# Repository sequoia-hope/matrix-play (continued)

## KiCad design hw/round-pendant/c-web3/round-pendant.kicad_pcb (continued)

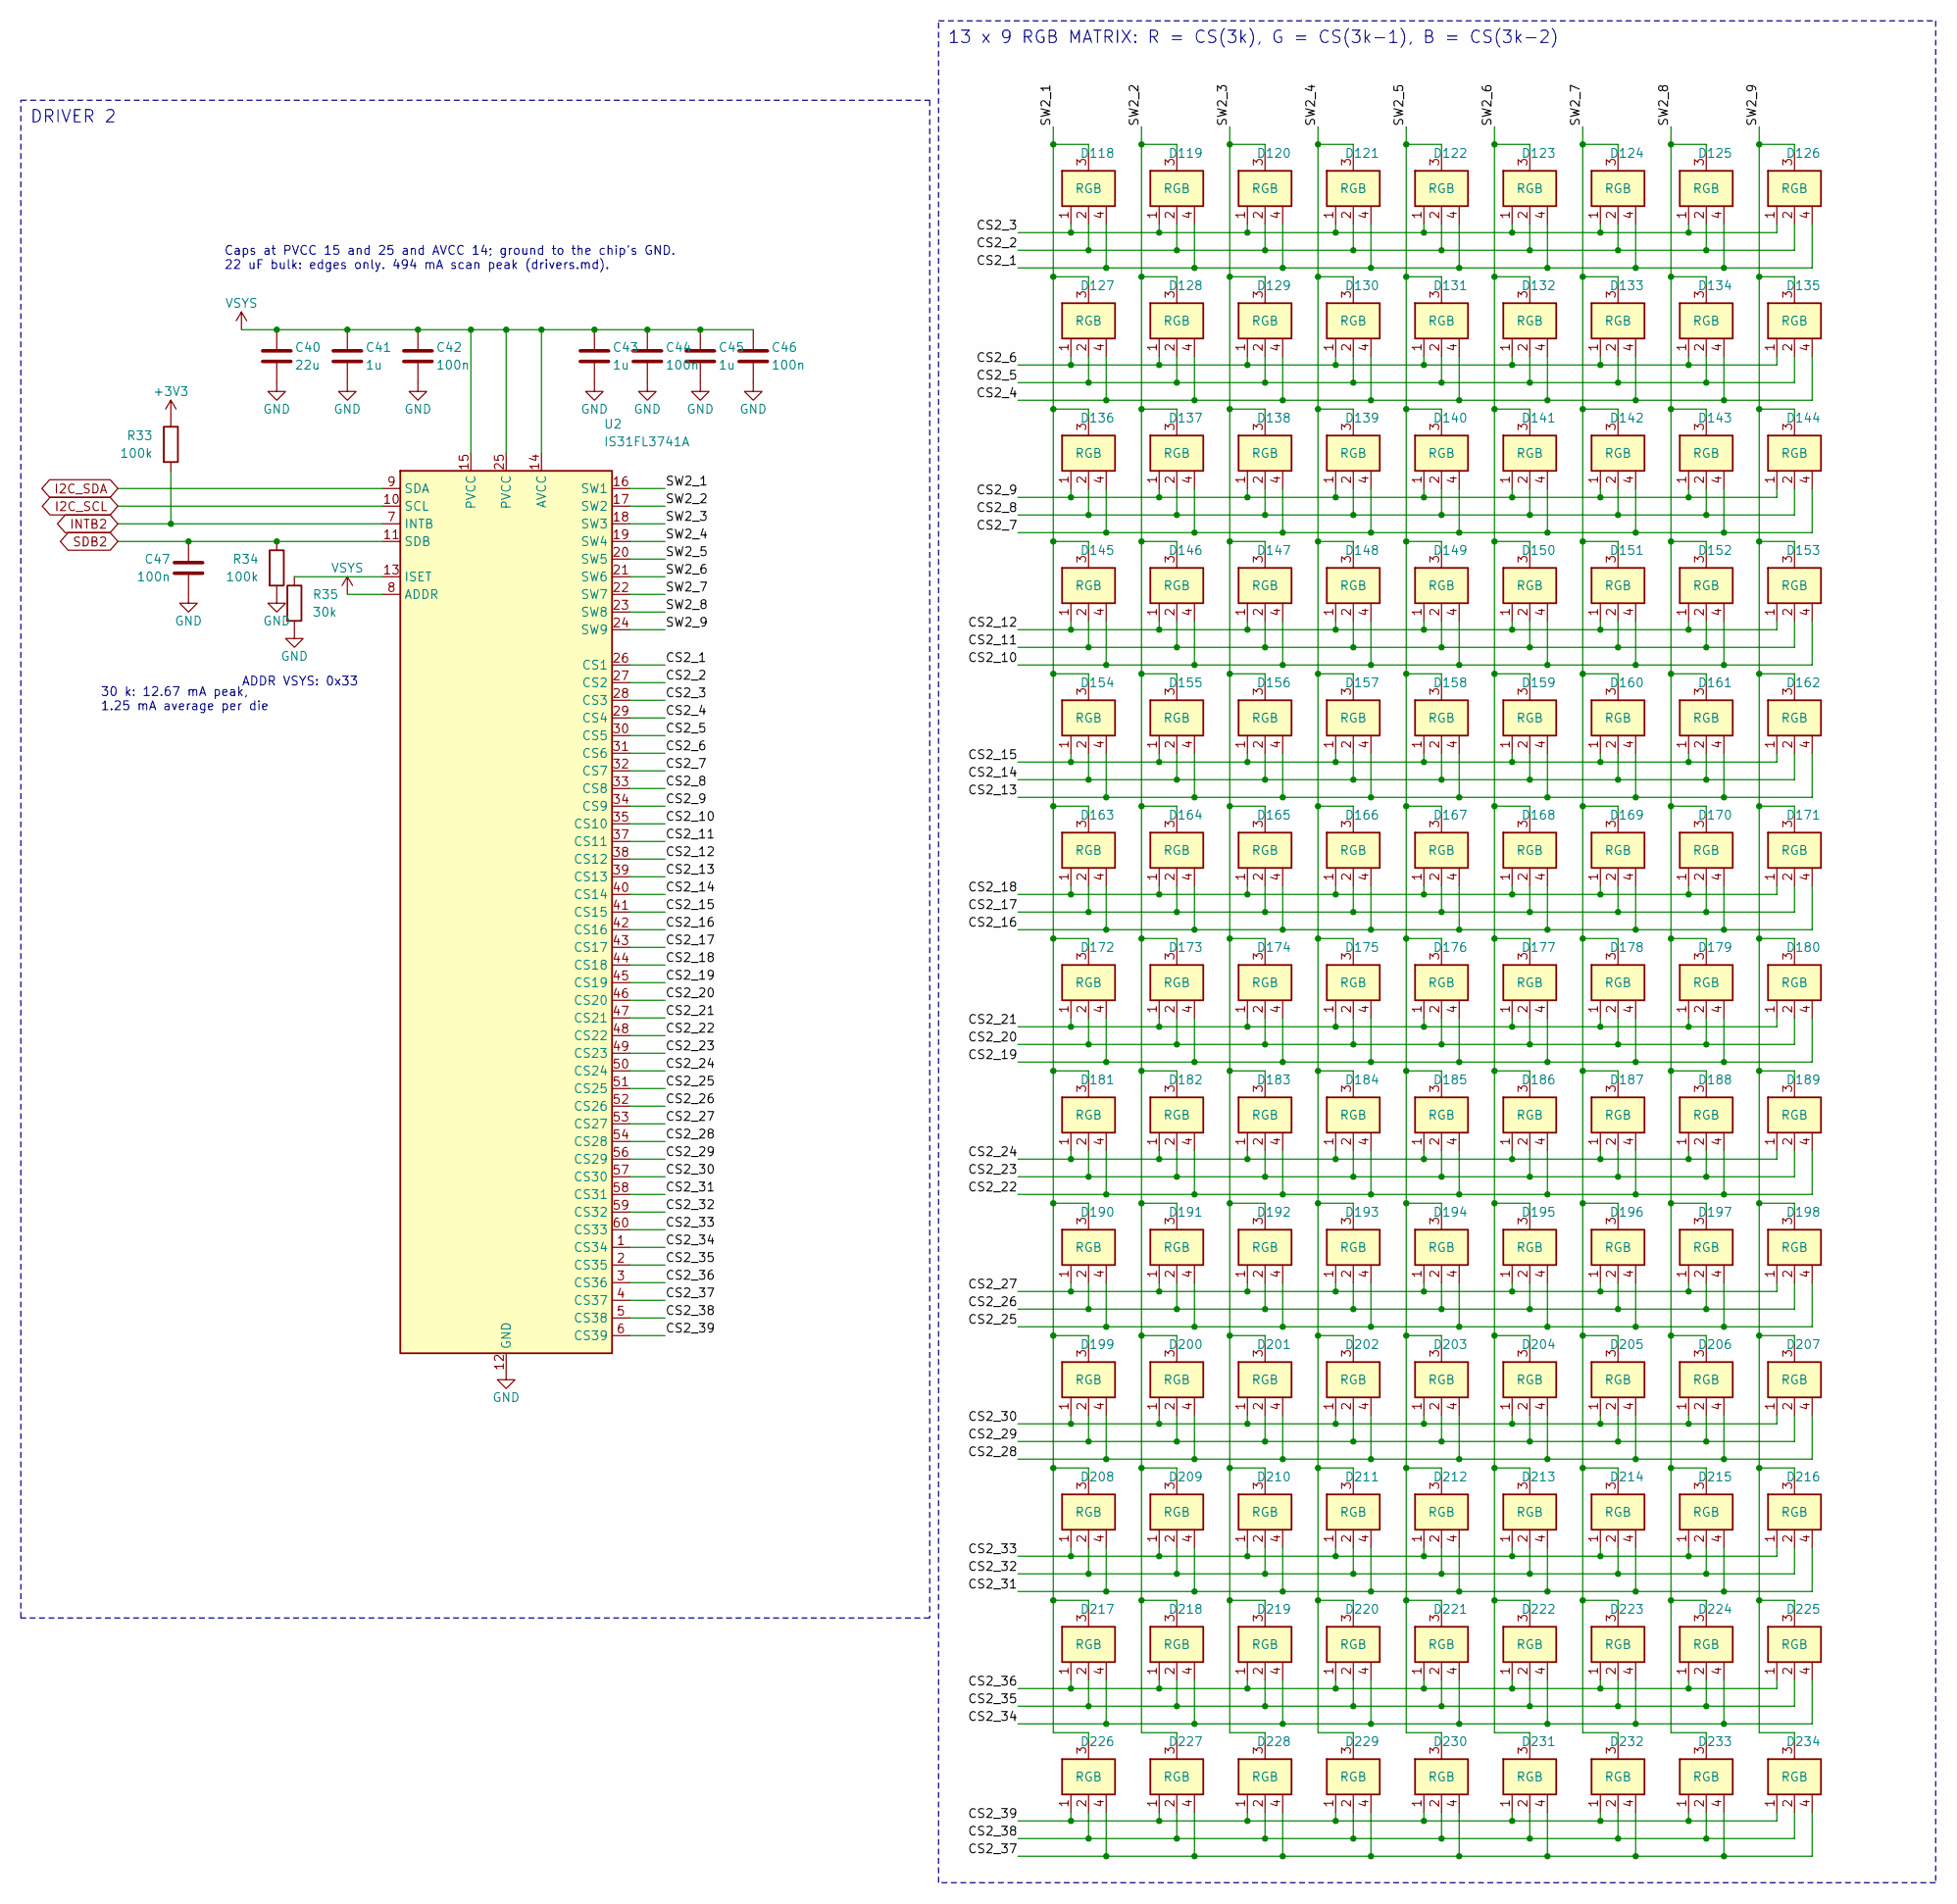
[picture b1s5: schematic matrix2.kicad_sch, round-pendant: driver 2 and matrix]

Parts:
C40: 22u; C_0603_1608Metric; MPN CL10A226MP8NUNE; LCSC C86295
C41, C43, C45: 1u; C_0402_1005Metric; MPN CL05A105KA5NQNC; LCSC C52923
C42, C44, C46, C47: 100n; C_0402_1005Metric; MPN CL05B104KO5NNNC; LCSC C1525
D118, D119, D120, D121, D122, D123, D124, D125, D126, D127, D128, D129, D130, D131, D132, D133, D134, D135, D136, D137, D138, D139, D140, D141, D142, D143, D144, D145, D146, D147, D148, D149, D150, D151, D152, D153, D154, D155, D156, D157, D158, D159, D160, D161, D162, D163, D164, D165, D166, D167, D168, D169, D170, D171, D172, D173, D174, D175, D176, D177, D178, D179, D180, D181, D182, D183, D184, D185, D186, D187, D188, D189, D190, D191, D192, D193, D194, D195, D196, D197, D198, D199, D200, D201, D202, D203, D204, D205, D206, D207, D208, D209, D210, D211, D212, D213, D214, D215, D216, D217, D218, D219, D220, D221, D222, D223, D224, D225, D226, D227, D228, D229, D230, D231, D232, D233, D234: RGB; LED_XL-1010RGB; MPN XL-1010RGB-YG; LCSC C965834
R33, R34: 100k; R_0402_1005Metric; MPN 0402WGF1003TCE; LCSC C25741
R35: 30k; R_0402_1005Metric; MPN 0402WGF3002TCE; LCSC C25776
U2: IS31FL3741A; QFN-60-1EP_7x7mm_P0.4mm_EP5.4x5.4mm; MPN IS31FL3741A-QFLS4-TR; LCSC C2940604

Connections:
+3V3: R33.1; also elsewhere on the board
/Driver 2 and matrix/CS2_1: D118.4 (B), D119.4 (B), D120.4 (B), D121.4 (B), D122.4 (B), D123.4 (B), D124.4 (B), D125.4 (B), D126.4 (B), U2.26 (CS1)
/Driver 2 and matrix/CS2_2: D118.2 (G), D119.2 (G), D120.2 (G), D121.2 (G), D122.2 (G), D123.2 (G), D124.2 (G), D125.2 (G), D126.2 (G), U2.27 (CS2)
/Driver 2 and matrix/CS2_3: D118.1 (R), D119.1 (R), D120.1 (R), D121.1 (R), D122.1 (R), D123.1 (R), D124.1 (R), D125.1 (R), D126.1 (R), U2.28 (CS3)
/Driver 2 and matrix/CS2_4: D127.4 (B), D128.4 (B), D129.4 (B), D130.4 (B), D131.4 (B), D132.4 (B), D133.4 (B), D134.4 (B), D135.4 (B), U2.29 (CS4)
/Driver 2 and matrix/CS2_5: D127.2 (G), D128.2 (G), D129.2 (G), D130.2 (G), D131.2 (G), D132.2 (G), D133.2 (G), D134.2 (G), D135.2 (G), U2.30 (CS5)
/Driver 2 and matrix/CS2_6: D127.1 (R), D128.1 (R), D129.1 (R), D130.1 (R), D131.1 (R), D132.1 (R), D133.1 (R), D134.1 (R), D135.1 (R), U2.31 (CS6)
/Driver 2 and matrix/CS2_7: D136.4 (B), D137.4 (B), D138.4 (B), D139.4 (B), D140.4 (B), D141.4 (B), D142.4 (B), D143.4 (B), D144.4 (B), U2.32 (CS7)
/Driver 2 and matrix/CS2_8: D136.2 (G), D137.2 (G), D138.2 (G), D139.2 (G), D140.2 (G), D141.2 (G), D142.2 (G), D143.2 (G), D144.2 (G), U2.33 (CS8)
/Driver 2 and matrix/CS2_9: D136.1 (R), D137.1 (R), D138.1 (R), D139.1 (R), D140.1 (R), D141.1 (R), D142.1 (R), D143.1 (R), D144.1 (R), U2.34 (CS9)
/Driver 2 and matrix/CS2_10: D145.4 (B), D146.4 (B), D147.4 (B), D148.4 (B), D149.4 (B), D150.4 (B), D151.4 (B), D152.4 (B), D153.4 (B), U2.35 (CS10)
/Driver 2 and matrix/CS2_11: D145.2 (G), D146.2 (G), D147.2 (G), D148.2 (G), D149.2 (G), D150.2 (G), D151.2 (G), D152.2 (G), D153.2 (G), U2.37 (CS11)
/Driver 2 and matrix/CS2_12: D145.1 (R), D146.1 (R), D147.1 (R), D148.1 (R), D149.1 (R), D150.1 (R), D151.1 (R), D152.1 (R), D153.1 (R), U2.38 (CS12)
/Driver 2 and matrix/CS2_13: D154.4 (B), D155.4 (B), D156.4 (B), D157.4 (B), D158.4 (B), D159.4 (B), D160.4 (B), D161.4 (B), D162.4 (B), U2.39 (CS13)
/Driver 2 and matrix/CS2_14: D154.2 (G), D155.2 (G), D156.2 (G), D157.2 (G), D158.2 (G), D159.2 (G), D160.2 (G), D161.2 (G), D162.2 (G), U2.40 (CS14)
/Driver 2 and matrix/CS2_15: D154.1 (R), D155.1 (R), D156.1 (R), D157.1 (R), D158.1 (R), D159.1 (R), D160.1 (R), D161.1 (R), D162.1 (R), U2.41 (CS15)
/Driver 2 and matrix/CS2_16: D163.4 (B), D164.4 (B), D165.4 (B), D166.4 (B), D167.4 (B), D168.4 (B), D169.4 (B), D170.4 (B), D171.4 (B), U2.42 (CS16)
/Driver 2 and matrix/CS2_17: D163.2 (G), D164.2 (G), D165.2 (G), D166.2 (G), D167.2 (G), D168.2 (G), D169.2 (G), D170.2 (G), D171.2 (G), U2.43 (CS17)
/Driver 2 and matrix/CS2_18: D163.1 (R), D164.1 (R), D165.1 (R), D166.1 (R), D167.1 (R), D168.1 (R), D169.1 (R), D170.1 (R), D171.1 (R), U2.44 (CS18)
/Driver 2 and matrix/CS2_19: D172.4 (B), D173.4 (B), D174.4 (B), D175.4 (B), D176.4 (B), D177.4 (B), D178.4 (B), D179.4 (B), D180.4 (B), U2.45 (CS19)
/Driver 2 and matrix/CS2_20: D172.2 (G), D173.2 (G), D174.2 (G), D175.2 (G), D176.2 (G), D177.2 (G), D178.2 (G), D179.2 (G), D180.2 (G), U2.46 (CS20)
/Driver 2 and matrix/CS2_21: D172.1 (R), D173.1 (R), D174.1 (R), D175.1 (R), D176.1 (R), D177.1 (R), D178.1 (R), D179.1 (R), D180.1 (R), U2.47 (CS21)
/Driver 2 and matrix/CS2_22: D181.4 (B), D182.4 (B), D183.4 (B), D184.4 (B), D185.4 (B), D186.4 (B), D187.4 (B), D188.4 (B), D189.4 (B), U2.48 (CS22)
/Driver 2 and matrix/CS2_23: D181.2 (G), D182.2 (G), D183.2 (G), D184.2 (G), D185.2 (G), D186.2 (G), D187.2 (G), D188.2 (G), D189.2 (G), U2.49 (CS23)
/Driver 2 and matrix/CS2_24: D181.1 (R), D182.1 (R), D183.1 (R), D184.1 (R), D185.1 (R), D186.1 (R), D187.1 (R), D188.1 (R), D189.1 (R), U2.50 (CS24)
/Driver 2 and matrix/CS2_25: D190.4 (B), D191.4 (B), D192.4 (B), D193.4 (B), D194.4 (B), D195.4 (B), D196.4 (B), D197.4 (B), D198.4 (B), U2.51 (CS25)
/Driver 2 and matrix/CS2_26: D190.2 (G), D191.2 (G), D192.2 (G), D193.2 (G), D194.2 (G), D195.2 (G), D196.2 (G), D197.2 (G), D198.2 (G), U2.52 (CS26)
/Driver 2 and matrix/CS2_27: D190.1 (R), D191.1 (R), D192.1 (R), D193.1 (R), D194.1 (R), D195.1 (R), D196.1 (R), D197.1 (R), D198.1 (R), U2.53 (CS27)
/Driver 2 and matrix/CS2_28: D199.4 (B), D200.4 (B), D201.4 (B), D202.4 (B), D203.4 (B), D204.4 (B), D205.4 (B), D206.4 (B), D207.4 (B), U2.54 (CS28)
/Driver 2 and matrix/CS2_29: D199.2 (G), D200.2 (G), D201.2 (G), D202.2 (G), D203.2 (G), D204.2 (G), D205.2 (G), D206.2 (G), D207.2 (G), U2.56 (CS29)
/Driver 2 and matrix/CS2_30: D199.1 (R), D200.1 (R), D201.1 (R), D202.1 (R), D203.1 (R), D204.1 (R), D205.1 (R), D206.1 (R), D207.1 (R), U2.57 (CS30)
/Driver 2 and matrix/CS2_31: D208.4 (B), D209.4 (B), D210.4 (B), D211.4 (B), D212.4 (B), D213.4 (B), D214.4 (B), D215.4 (B), D216.4 (B), U2.58 (CS31)
/Driver 2 and matrix/CS2_32: D208.2 (G), D209.2 (G), D210.2 (G), D211.2 (G), D212.2 (G), D213.2 (G), D214.2 (G), D215.2 (G), D216.2 (G), U2.59 (CS32)
/Driver 2 and matrix/CS2_33: D208.1 (R), D209.1 (R), D210.1 (R), D211.1 (R), D212.1 (R), D213.1 (R), D214.1 (R), D215.1 (R), D216.1 (R), U2.60 (CS33)
/Driver 2 and matrix/CS2_34: D217.4 (B), D218.4 (B), D219.4 (B), D220.4 (B), D221.4 (B), D222.4 (B), D223.4 (B), D224.4 (B), D225.4 (B), U2.1 (CS34)
/Driver 2 and matrix/CS2_35: D217.2 (G), D218.2 (G), D219.2 (G), D220.2 (G), D221.2 (G), D222.2 (G), D223.2 (G), D224.2 (G), D225.2 (G), U2.2 (CS35)
/Driver 2 and matrix/CS2_36: D217.1 (R), D218.1 (R), D219.1 (R), D220.1 (R), D221.1 (R), D222.1 (R), D223.1 (R), D224.1 (R), D225.1 (R), U2.3 (CS36)
/Driver 2 and matrix/CS2_37: D226.4 (B), D227.4 (B), D228.4 (B), D229.4 (B), D230.4 (B), D231.4 (B), D232.4 (B), D233.4 (B), D234.4 (B), U2.4 (CS37)
/Driver 2 and matrix/CS2_38: D226.2 (G), D227.2 (G), D228.2 (G), D229.2 (G), D230.2 (G), D231.2 (G), D232.2 (G), D233.2 (G), D234.2 (G), U2.5 (CS38)
/Driver 2 and matrix/CS2_39: D226.1 (R), D227.1 (R), D228.1 (R), D229.1 (R), D230.1 (R), D231.1 (R), D232.1 (R), D233.1 (R), D234.1 (R), U2.6 (CS39)
/Driver 2 and matrix/SW2_1: D118.3 (A), D127.3 (A), D136.3 (A), D145.3 (A), D154.3 (A), D163.3 (A), D172.3 (A), D181.3 (A), D190.3 (A), D199.3 (A), D208.3 (A), D217.3 (A), D226.3 (A), U2.16 (SW1)
/Driver 2 and matrix/SW2_2: D119.3 (A), D128.3 (A), D137.3 (A), D146.3 (A), D155.3 (A), D164.3 (A), D173.3 (A), D182.3 (A), D191.3 (A), D200.3 (A), D209.3 (A), D218.3 (A), D227.3 (A), U2.17 (SW2)
/Driver 2 and matrix/SW2_3: D120.3 (A), D129.3 (A), D138.3 (A), D147.3 (A), D156.3 (A), D165.3 (A), D174.3 (A), D183.3 (A), D192.3 (A), D201.3 (A), D210.3 (A), D219.3 (A), D228.3 (A), U2.18 (SW3)
/Driver 2 and matrix/SW2_4: D121.3 (A), D130.3 (A), D139.3 (A), D148.3 (A), D157.3 (A), D166.3 (A), D175.3 (A), D184.3 (A), D193.3 (A), D202.3 (A), D211.3 (A), D220.3 (A), D229.3 (A), U2.19 (SW4)
/Driver 2 and matrix/SW2_5: D122.3 (A), D131.3 (A), D140.3 (A), D149.3 (A), D158.3 (A), D167.3 (A), D176.3 (A), D185.3 (A), D194.3 (A), D203.3 (A), D212.3 (A), D221.3 (A), D230.3 (A), U2.20 (SW5)
/Driver 2 and matrix/SW2_6: D123.3 (A), D132.3 (A), D141.3 (A), D150.3 (A), D159.3 (A), D168.3 (A), D177.3 (A), D186.3 (A), D195.3 (A), D204.3 (A), D213.3 (A), D222.3 (A), D231.3 (A), U2.21 (SW6)
/Driver 2 and matrix/SW2_7: D124.3 (A), D133.3 (A), D142.3 (A), D151.3 (A), D160.3 (A), D169.3 (A), D178.3 (A), D187.3 (A), D196.3 (A), D205.3 (A), D214.3 (A), D223.3 (A), D232.3 (A), U2.22 (SW7)
/Driver 2 and matrix/SW2_8: D125.3 (A), D134.3 (A), D143.3 (A), D152.3 (A), D161.3 (A), D170.3 (A), D179.3 (A), D188.3 (A), D197.3 (A), D206.3 (A), D215.3 (A), D224.3 (A), D233.3 (A), U2.23 (SW8)
/Driver 2 and matrix/SW2_9: D126.3 (A), D135.3 (A), D144.3 (A), D153.3 (A), D162.3 (A), D171.3 (A), D180.3 (A), D189.3 (A), D198.3 (A), D207.3 (A), D216.3 (A), D225.3 (A), D234.3 (A), U2.24 (SW9)
I2C_SCL: U2.10 (SCL); also elsewhere on the board
I2C_SDA: U2.9 (SDA); also elsewhere on the board
INTB2: R33.2, U2.7 (INTB); also elsewhere on the board
unnamed: R35.1, U2.13 (ISET)
SDB2: C47.1, R34.1, U2.11 (SDB); also elsewhere on the board
VSYS: C40.1, C41.1, C42.1, C43.1, C44.1, C45.1, C46.1, U2.8 (ADDR), U2.14 (AVCC), U2.15 (PVCC), U2.25 (PVCC); also elsewhere on the board

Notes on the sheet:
Caps at PVCC 15 and 25 and AVCC 14; ground to the chip's GND. 22 uF bulk: edges only. 494 mA scan peak (drivers.md).
ADDR VSYS: 0x33
30 k: 12.67 mA peak, 1.25 mA average per die
DRIVER 2
13 x 9 RGB MATRIX: R = CS(3k), G = CS(3k-1), B = CS(3k-2)

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
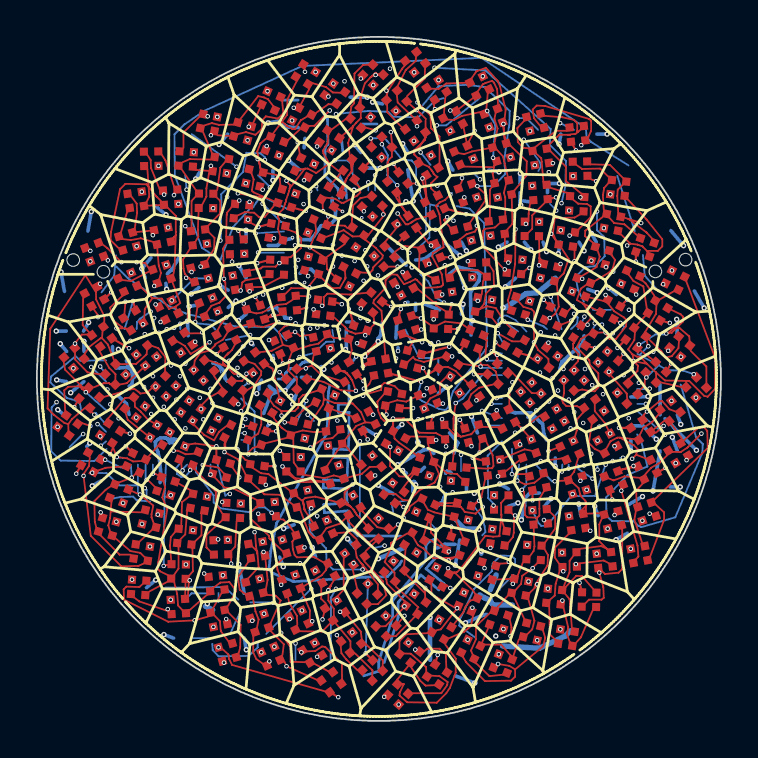
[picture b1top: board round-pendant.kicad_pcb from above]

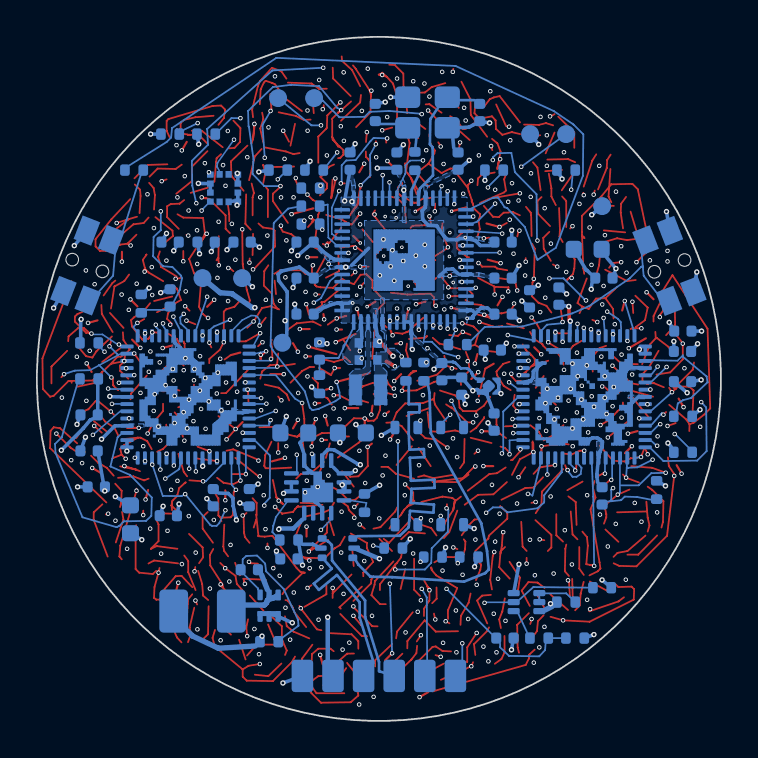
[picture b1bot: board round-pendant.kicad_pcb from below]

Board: 8 copper layers, 38.0 x 38.0 mm, 332 parts (97 on the bottom side), 155 nets.

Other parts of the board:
D235: RGB; LED_XL-1010RGB
R40: 1k; R_0402_1005Metric
R41, R42: 470R; R_0402_1005Metric

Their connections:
+3V3: D235.3; also elsewhere on the board
/MCU/CLED_B: R42.1; also elsewhere on the board
/MCU/CLED_G: R41.1; also elsewhere on the board
/MCU/CLED_R: R40.1; also elsewhere on the board
unnamed: D235.4, R42.2
unnamed: D235.2, R41.2
unnamed: D235.1, R40.2

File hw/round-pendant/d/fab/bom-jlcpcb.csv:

Comment,Designator,Footprint,LCSC Part #,MPN,Manufacturer
1u,"C1,C3,C4,C31,C34,C41,C44,C51,C54,C61,C64,C71,C74",C_0402_1005Metric,C52923,CL05A105KA5NQNC,Samsung Electro-Mechanics
22u,"C2,C30,C40",C_0603_1608Metric,C86295,CL10A226MP8NUNE,Samsung Electro-Mechanics
10u,C5,C_0603_1608Metric,C19702,CL10A106KP8NNNC,Samsung Electro-Mechanics
100n,"C6,C7,C8,C9,C10,C11,C12,C13,C14,C20,C21,C22,C25,C27,C32,C33,C35,C42,C43,C52,C53,C62,C63,C72,C73",C_0402_1005Metric,C1525,CL05B104KO5NNNC,Samsung Electro-Mechanics
4.7u,"C16,C18",C_0402_1005Metric_small_pads,C23733,CL05A475MP5NRNC,Samsung Electro-Mechanics
4.7u,"C17,C19,C26",C_0402_1005Metric,C23733,CL05A475MP5NRNC,Samsung Electro-Mechanics
15p,"C23,C24",C_0402_1005Metric,C1548,0402CG150J500NT,FH
RGB,"D1,D2,D3,D4,D5,D6,D7,D8,D9,D10,D11,D12,D13,D14,D15,D16,D17,D18,D19,D20,D21,D22,D23,D24,D25,D26,D27,D28,D29,D30,D31,D32,D33,D34,D35,D36,D37,D38,D39,D40,D41,D42,D43,D44,D45,D46,D47,D48,D49,D50,D51,D52,D53,D54,D55,D56,D57,D58,D59,D60,D61,D62,D63,D64,D65,D66,D67,D68,D69,D70,D71,D72,D73,D74,D75,D76,D77,D78,D79,D80,D81,D82,D83,D84,D85,D86,D87,D88,D89,D90,D91,D92,D93,D94,D95,D96,D97,D98,D99,D100,D101,D102,D103,D104,D105,D106,D107,D108,D109,D110,D111,D112,D113,D114,D115,D116,D117,D118,D119,D120,D121,D122,D123,D124,D125,D126,D127,D128,D129,D130,D131,D132,D133,D134,D135,D136,D137,D138,D139,D140,D141,D142,D143,D144,D145,D146,D147,D148,D149,D150,D151,D152,D153,D154,D155,D156,D157,D158,D159,D160,D161,D162,D163,D164,D165,D166,D167,D168,D169,D170,D171,D172,D173,D174,D175,D176,D177,D178,D179,D180,D181,D182,D183,D184,D185,D186,D187,D188,D189,D190,D191,D192,D193,D194,D195,D196,D197,D198,D199,D200,D201,D202,D203,D204,D205,D206,D207,D208,D209,D210,D211,D212,D213,D214,D215,D216,D217,D218,D219,D220,D221,D222,D223,D224,D225,D226,D227,D228,D229,D230,D231,D232,D233,D234,D235",LED_XL-1010RGB,C965834,XL-1010RGB-YG,XINGLIGHT
3.3u,L1,L_pol_2016,C42411119,AOTA-B201610S3R3-101-T,Abracon
NTZD3155C,Q1,SOT-563,C236117,NTZD3155CT1G,onsemi
5.1k,"R1,R2",R_0402_1005Metric,C25905,0402WGF5101TCE,UNI-ROYAL
10k,R3,R_0402_1005Metric,C25744,0402WGF1002TCE,UNI-ROYAL
3k,R4,R_0402_1005Metric,C25784,0402WGF3001TCE,UNI-ROYAL
3.6k,R5,R_0402_1005Metric,C25891,0402WGF3601TCE,UNI-ROYAL
100k,"R6,R7,R9,R10,R11,R12,R31",R_0402_1005Metric,C25741,0402WGF1003TCE,UNI-ROYAL
100R,R8,R_0402_1005Metric,C25076,0402WGF1000TCE,UNI-ROYAL
33R,R13,R_0402_1005Metric,C25105,0402WGF330JTCE,UNI-ROYAL
27R,"R14,R15",R_0402_1005Metric,C25100,0402WGF270JTCE,UNI-ROYAL
1k,"R16,R17,R18,R21,R22",R_0402_1005Metric,C11702,0402WGF1001TCE,UNI-ROYAL
4.7k,"R19,R20",R_0402_1005Metric,C25900,0402WGF4701TCE,UNI-ROYAL
30k,"R30,R33,R50,R60,R70",R_0402_1005Metric,C25776,0402WGF3002TCE,UNI-ROYAL
USER / WAKE,SW1,SW_Panasonic_EVQP7C,C388883,EVQP7C01P,PANASONIC
BOOTSEL,SW2,SW_Panasonic_EVQP7C,C388883,EVQP7C01P,PANASONIC
IS31FL3745,"U1,U2,U10,U11,U12",WLCSP-36_2.9x2.9mm_P0.5mm,C2678907,IS31FL3745-CLS4-TR,ISSI
RP2350A,U3,RP2350-QFN-60-1EP_7x7_P0.4mm_EP3.4x3.4mm_ThermalVias,C42411118,RP2350A,Raspberry Pi
W25Q128JVPIQ,U4,WSON-8_6x5mm_P1.27mm_NoEPCopper,C190862,W25Q128JVPIQ,Winbond
BQ24073,U5,QFN-16-1EP_3x3mm_P0.5mm_EP1.7x1.7mm,C15220,BQ24073RGTR,Texas Instruments
TPS7A0233,U6,Texas_X2SON-4_1x1mm_P0.65mm,C2860046,TPS7A0233PDQNR,Texas Instruments
USBLC6-2P6,U7,SOT-666,C15999,USBLC6-2P6,STMicroelectronics
XB9901A,U8,XySemi_DFN-6_1.8x1.4mm,C669687,XB9901A,XySemi
LIS2DW12,U9,LGA-12_2x2mm_P0.5mm,C189624,LIS2DW12TR,STMicroelectronics
12MHz,Y1,Crystal_SMD_3225-4Pin_3.2x2.5mm,C20625731,ABM8-272-T3,Abracon
